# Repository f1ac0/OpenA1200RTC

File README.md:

# OpenA1200RTC
OpenA1200RTC is an Open Hardware RTC module for the Amiga 1200 by screwbreaker and Sukkopera : https://github.com/screwbreaker/OpenA1200RTC.

This project is a different layout of the board, with almost the same BOM :
- shorter pin header,
- no jumper to disable the board,
- footprint for CR1220 and wired cell in addition to the CR2032.

# Disclaimer
This is a hobbyist project, it comes with no warranty and no support.

I publish this work using the same license as the original project : "Open Hardware. If you make any modifications to the board, please contribute them back".

If you find it useful, please reward the original authors.

# BOM
- 1x RTC62421
- 1x 2x11 2.0mm pin socket
- 1x 2.2uF 0805 capacitor
- 1x 100nF 0805 capacitor
- 1x BAT721C or BAT54C diodes
- 2x 220 ohm 0805 resistor
- 3x 10k ohm 0805 resistor
- 1x battery holder : CR1220, CR2032 or pin header

# Making it
Make sure that the chip is working before soldering it.

If you plan to use a battery holder, make sure that the RTC62421 is not fully inserted and that its leads and your solder joints do not stick out of the holes in PCB. Thanks to this, the holder will be able to lay flat on the PCB.

Check for shorts at least between 5V and GND traces before applying power !

# Using it
- Install the battery,
- Plug on the motherboard,
- Power on the system.

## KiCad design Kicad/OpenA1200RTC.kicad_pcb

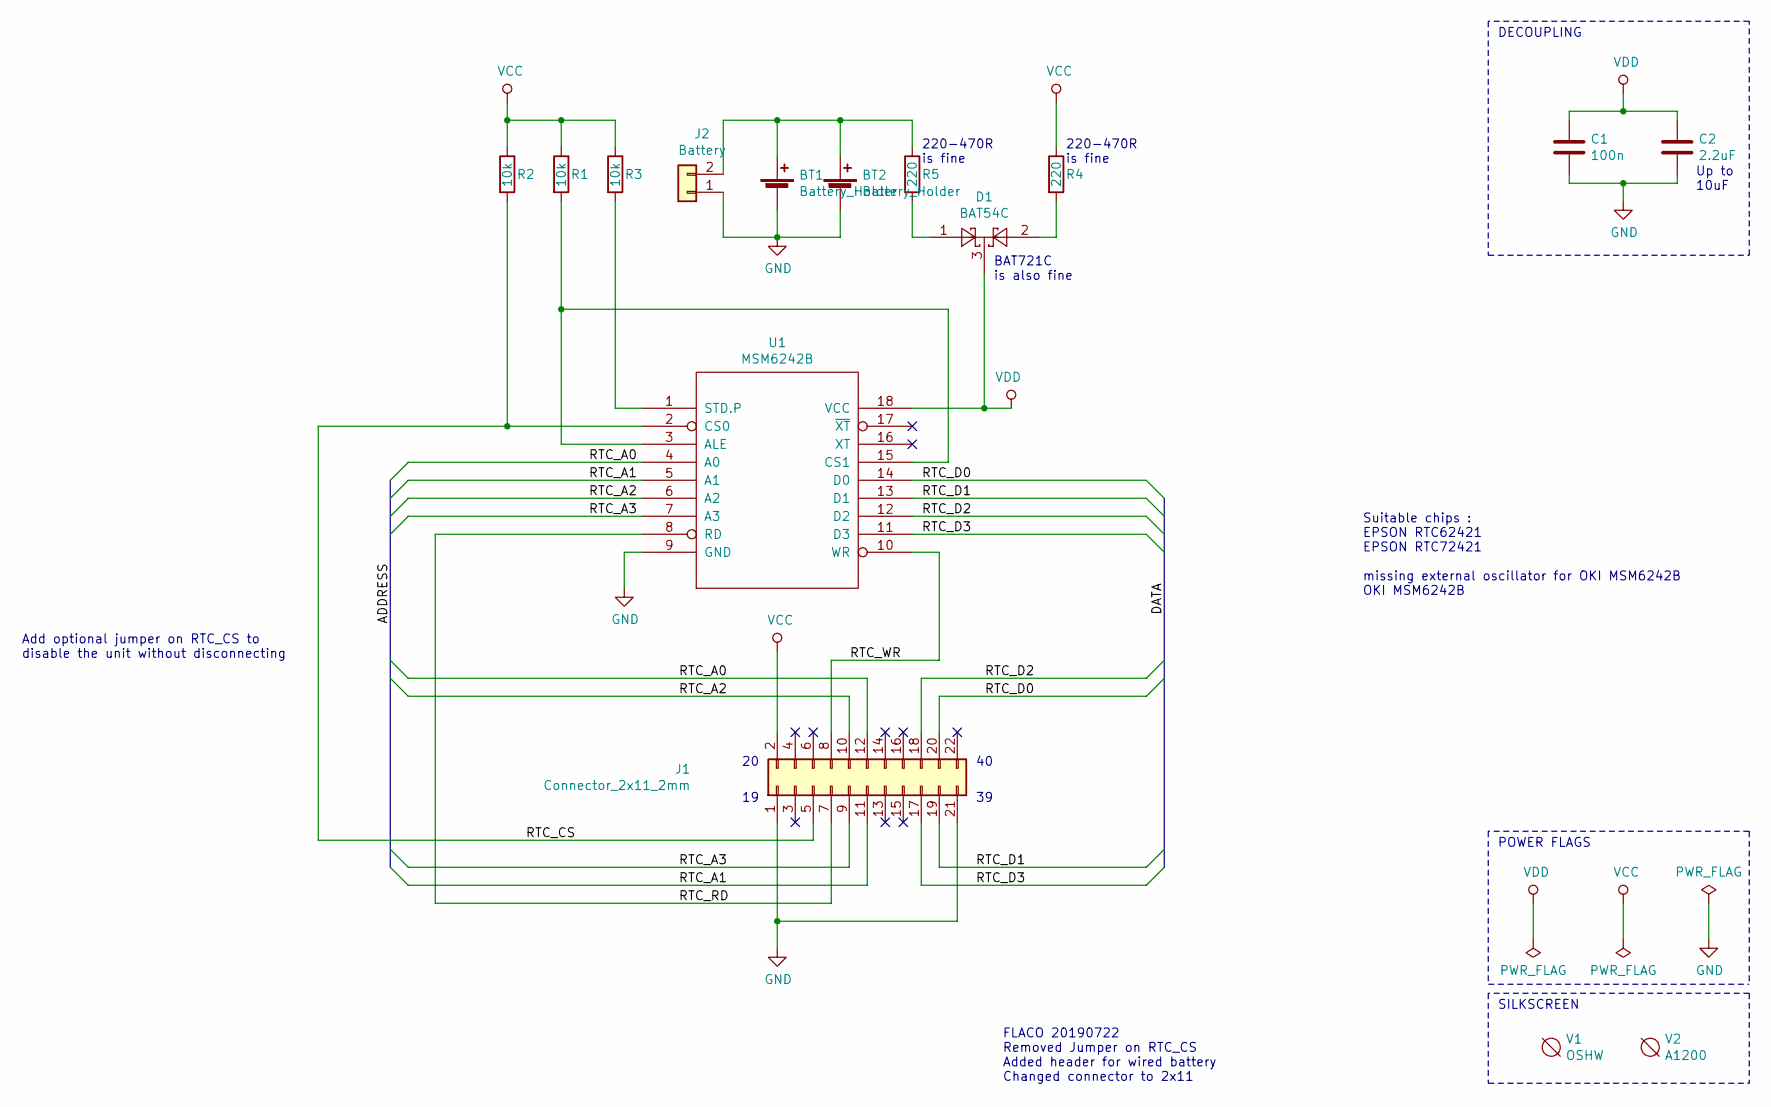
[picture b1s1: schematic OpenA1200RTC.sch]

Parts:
BT1: Battery_Holder; Battery_Holder_Coin_2032_BS-7
BT2: Battery_Holder; Battery_Holder_Coin_1220_BS-1220-1
C1: 100n; C_0805_HandSoldering
C2: 2.2uF; C_1206_HandSoldering
D1: BAT54C; SOT-23_Handsoldering
J1: Connector_2x11_2mm; Socket_Strip_Straight_2x11_Pitch2.00mm
J2: Battery; Pin_Header_Straight_1x02_Pitch2.54mm
R1, R2, R3: 10k; R_0805_HandSoldering
R4: 220; R_0805_HandSoldering
R5: 220; R_0805
U1: MSM6242B; DIP-18_W7.62mm_Socket
V1: OSHW; OSHW-Logo_5.7x6mm_SilkScreen
V2: A1200

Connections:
/RTC_A0: J1.12, U1.4 (A0)
/RTC_A1: J1.11, U1.5 (A1)
/RTC_A2: J1.10, U1.6 (A2)
/RTC_A3: J1.9, U1.7 (A3)
/RTC_CS: J1.5, R2.2, U1.2 (CS0)
/RTC_D0: J1.20, U1.14 (D0)
/RTC_D1: J1.19, U1.13 (D1)
/RTC_D2: J1.18, U1.12 (D2)
/RTC_D3: J1.17, U1.11 (D3)
/RTC_RD: J1.7, U1.8 (RD)
/RTC_WR: J1.8, U1.10 (WR)
GND: BT1.2 (-), BT2.2 (-), C1.2, C2.2, J1.1, J1.21, J2.1, U1.9 (GND)
unnamed: BT1.1 (+), BT2.1 (+), J2.2, R5.1
unnamed: D1.1, R5.2
unnamed: D1.2, R4.2
unnamed: R1.2, U1.3 (ALE), U1.15 (CS1)
unnamed: R3.2, U1.1 (STD.P)
VCC: J1.2, R1.1, R2.1, R3.1, R4.1
VDD: C1.1, C2.1, D1.3, U1.18 (VCC)

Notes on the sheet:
DECOUPLING
POWER FLAGS
Up to 10uF
SILKSCREEN
220-470R is fine
BAT721C is also fine
Add optional jumper on RTC_CS to disable the unit without disconnecting
Suitable chips : EPSON RTC62421 EPSON RTC72421 missing external oscillator for OKI MSM6242B OKI MSM6242B
FLACO 20190722 Removed Jumper on RTC_CS Added header for wired battery Changed connector to 2x11

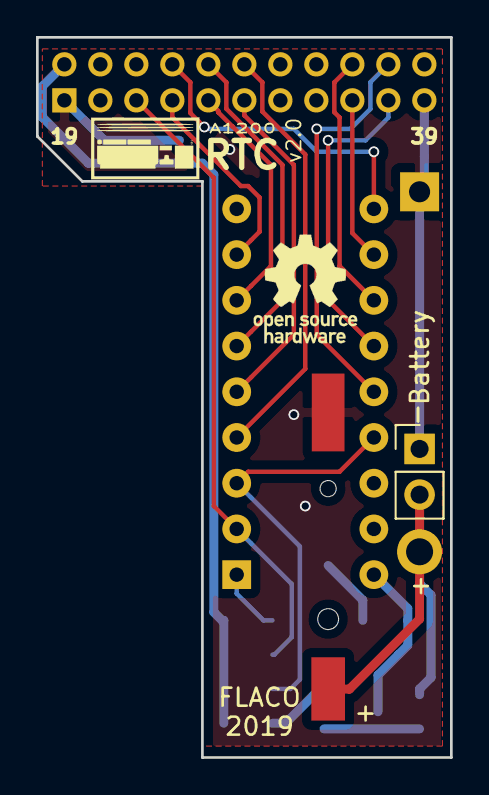
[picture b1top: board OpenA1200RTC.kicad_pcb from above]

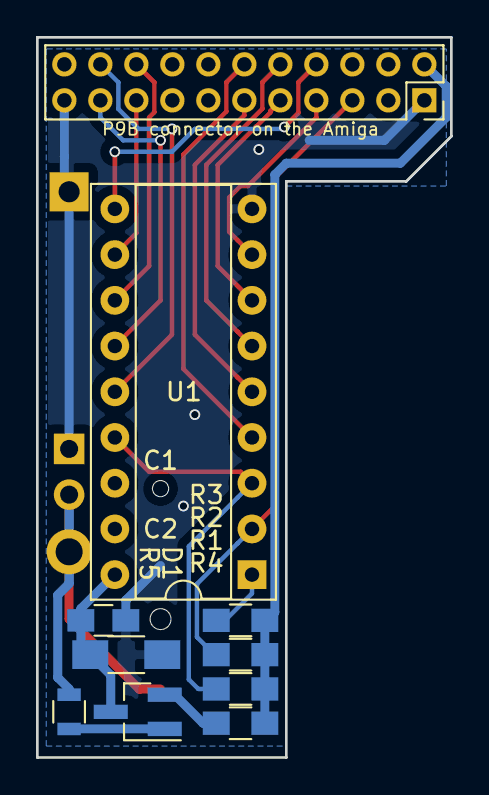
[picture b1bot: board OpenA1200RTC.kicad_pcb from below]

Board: 2 copper layers, 23.0 x 40.0 mm, 15 parts (10 on the bottom side), 19 nets.

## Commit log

2020-09-08 Repository init with KiCAD files and Readme
2022-02-15 Photo and InteractiveHtmlBom
